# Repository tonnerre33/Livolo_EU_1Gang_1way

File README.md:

# Linovo_EU_1Gang_1way

# What is this ?

It's a livolo EU 1 Gang 1 Way adapter for make it compatible with Mysensors.

You have just to build this node and replace the front plate of your Livolo EU Switch and you'll be able to command your light with your Mysensors controller.

This node is compatible with livolo **EU VL-C701X-2 VER:C0**

# Warning !!

**I'm not responsible if the Livolo manufacturer change the board hardware revision or if you bought the wrong product !**

# Why i'm working with this switch ?

## Run without neutral wire (2 wires system) :

I leave in France and we are only 2 wires for the light switch. 

For the moment, there is no mysensors project for 2 wires installation.

The Linovo EU switch is a 2 wires project !!

## No need more place in your wall :

Who has never been a lack of a place in his wall box ?

This product can be installed in your existing wall box in place of your interruptor without a problem !!

## Touch Pad and beautifull design :

Maybe it's the future ? 

So you'll have an ultimate beauty and you'll be able to command your light with a sensitive touch control feeling like iPhone touch.

## Seems pretty  safe :

I don't know for you, but i am pretty scared about fire with electronic in my walls. 

That's why i don't want to put any electronical card in my walls without case and this switch has a one.

## More informations about the switch :

https://fr.aliexpress.com/item/Free-Shipping-Livolo-Luxury-White-Crystal-Glass-Switch-Panel-EU-Standard-VL-C701-11-110-250V/512886492.html# Livolo_EU_1Gang_1way

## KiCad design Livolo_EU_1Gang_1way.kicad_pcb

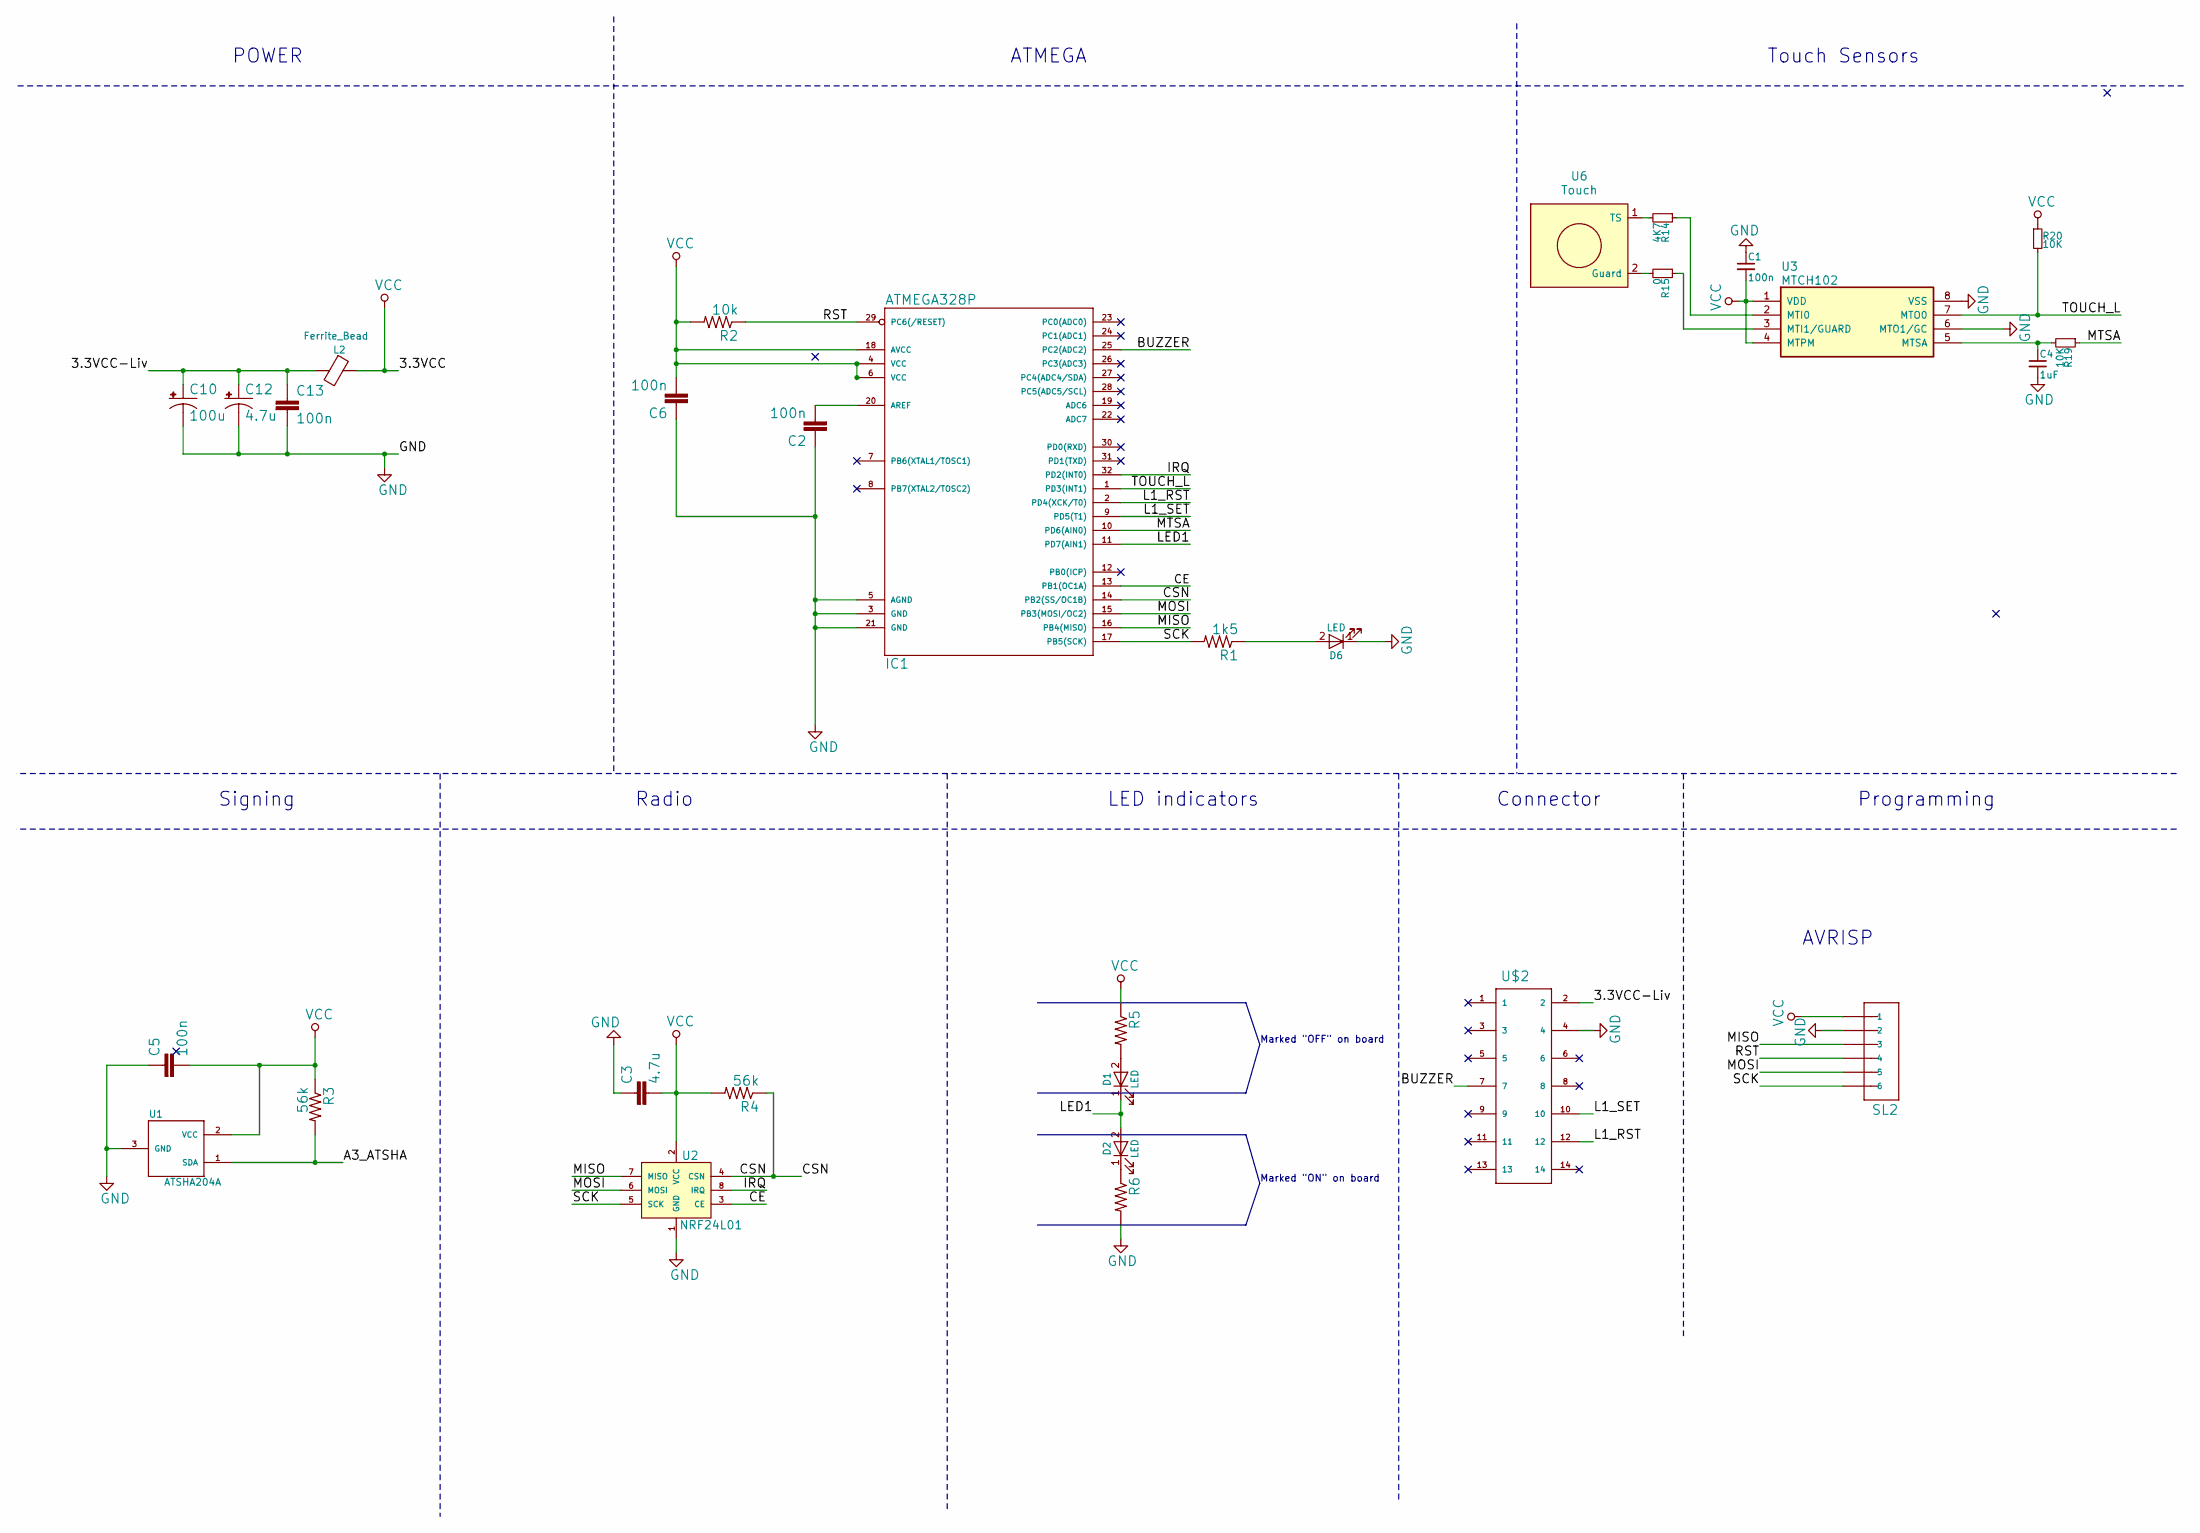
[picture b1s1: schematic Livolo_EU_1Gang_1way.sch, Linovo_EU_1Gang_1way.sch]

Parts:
C1, C5: 100n; C_0603_HandSoldering
C2, C6: 100n; C_0402
C3: 4.7u; C_0603_HandSoldering
C4: 1uF; C_0603_HandSoldering
C10: 100u; EIA3216; Rating X5R/10V
C12: 4.7u; EIA3216; Rating X5R/10V
C13: 100n; C_0603_HandSoldering; Rating X5R/10V
D1, D2, D6: LED; LED_0603
IC1: ATMEGA328P; TQFP32-08
L2: Ferrite_Bead; R_0603_HandSoldering
R1: 1k5; R_0603_HandSoldering
R2: 10k; R_0603_HandSoldering
R3, R4: 56k; R_0603_HandSoldering
R5, R6: R_0603_HandSoldering
R14: 4K7; R_0603
R15: 0; R_0603
R19, R20: 10K; R_0603
SL2: 1X06-1MM
U1: ATSHA204A; SOT23-3
U2: NRF24L01; NRF24L01-SMD
U3: MTCH102; MSOP-8_3x3mm_Pitch0.65mm
U6: Touch; livolo_ts_guard
U$2: CONNECTOR_02_X_072MM_SPACING; CONNECTOR_02_X_07_2MM

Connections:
/3.3VCC-Liv: C10.+, C12.+, C13.1, L2.2, U$2.2
/A3_ATSHA: R3.2, U1.1 (SDA)
/BUZZER: IC1.25 (PC2(ADC2)), U$2.7
/CE: IC1.13 (PB1(OC1A)), U2.3 (CE)
/CSN: IC1.14 (PB2(SS/OC1B)), R4.1, U2.4 (CSN)
/IRQ: IC1.32 (PD2(INT0)), U2.8 (IRQ)
/L1_RST: IC1.2 (PD4(XCK/T0)), U$2.12
/L1_SET: IC1.9 (PD5(T1)), U$2.10
/LED1: D1.1 (K), D2.2 (A), IC1.11 (PD7(AIN1))
/MISO: IC1.16 (PB4(MISO)), SL2.3, U2.7 (MISO)
/MOSI: IC1.15 (PB3(MOSI/OC2)), SL2.5, U2.6 (MOSI)
/MTSA: IC1.10 (PD6(AIN0)), R19.1
/RST: IC1.29 (PC6(/RESET)), R2.1, SL2.4
/SCK: IC1.17 (PB5(SCK)), R1.2, SL2.6, U2.5 (SCK)
/TOUCH_L: IC1.1 (PD3(INT1)), R20.2, U3.7 (MTO0)
GND: C1.1, C2.1, C3.1, C4.2, C5.1, C6.1, C10.-, C12.-, C13.2, D6.1 (K), IC1.3 (GND), IC1.5 (AGND), IC1.21 (GND), R6.2, SL2.2, U1.3 (GND), U2.1 (GND), U3.6 (MTO1/GC), U3.8 (VSS), U$2.4
unnamed: C2.2, IC1.20 (AREF)
unnamed: C4.1, R19.2, U3.5 (MTSA)
unnamed: D1.2 (A), R5.2
unnamed: D2.1 (K), R6.1
unnamed: D6.2 (A), R1.1
unnamed: R14.1, U3.2 (MTI0)
unnamed: R14.2, U6.1 (TS)
unnamed: R15.1, U3.3 (MTI1/GUARD)
unnamed: R15.2, U6.2 (Guard)
VCC: C1.2, C3.2, C5.2, C6.2, IC1.4 (VCC), IC1.6 (VCC), IC1.18 (AVCC), L2.1, R2.2, R3.1, R4.2, R5.1, R20.1, SL2.1, U1.2 (VCC), U2.2 (VCC), U3.1 (VDD), U3.4 (MTPM)

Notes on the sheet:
Programming
AVRISP
Touch Sensors
ATMEGA
POWER
Signing
Radio
LED indicators
Marked "OFF" on board
Marked "ON" on board
Connector

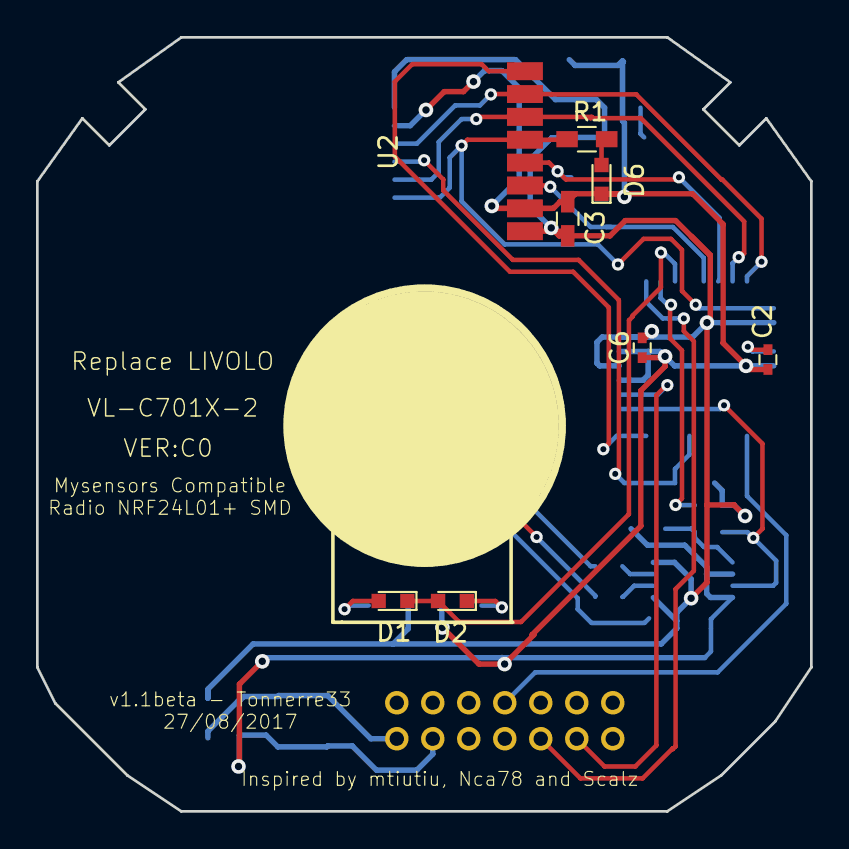
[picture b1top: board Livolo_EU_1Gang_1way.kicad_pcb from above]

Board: 2 copper layers, 43.0 x 43.0 mm, 30 parts (0 on the bottom side), 26 nets.

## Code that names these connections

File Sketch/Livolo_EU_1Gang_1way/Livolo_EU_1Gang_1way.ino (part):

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int ledPins[] = {7};
byte buttonPins[] = {3};
const uint8_t RELAY_CH_PINS[][2] = {
    {5, 4} // channel 1 relay control pins(bistable relay - 2 coils) {L1_SET, L1_RST}

};
#define MTSA_PIN 6
#define BUZZER_PIN A2


const uint32_t RELAY_PULSE_DELAY_MS = 40; //Def 50
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    // initialize led, relays pins as outputs and buttons as inputs

    //SENSIBILITY
    pinMode(MTSA_PIN, OUTPUT);
    analogWrite(MTSA_PIN, 255 - settings.button_sensiblity * 255/100);
    //BUZZER
    pinMode(BUZZER_PIN, OUTPUT);
    digitalWrite(BUZZER_PIN, LOW);
    for (int i = 0; i < NUMBER_OF_BUTTONS; i++) {
        //LEDS
        pinMode(ledPins[i], OUTPUT);
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        if((millis() - lastMode) >= MODE_CLEANING_MS && MODE[i] == MODE_CLEANING) {
            MODE[0] = settings.mode_def[0];
            MODE[1] = settings.mode_def[1];
            blinkNumberOutput(1, BUZZER_PIN,100,100);
             for (int i = 0; i < NUMBER_OF_BUTTONS; i++) {
                digitalWrite(ledPins[i],  getChannelState(i));
             }
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                        switchLight(i+1, channelState[i]);
                        EndWaitFalseTrigger[i] = true;
                    } else {
                        blinkNumberOutput(1, BUZZER_PIN,100,100);
                    }
                }
            }
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                        MODE[i] = MODE_NORMAL;
                        channelState[i] = ON;
                        switchLight(i+1, channelState[i]); // No buzzer on the sleep power
                        blinkNumberOutput(2, BUZZER_PIN,100,100);
                    }
                    if(lastTouchTimestamp[i] >= LONG_TOUCH_DETECT_CLEANING_MS) {
                        MODE[0] = MODE_CLEANING;
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                        lastMode = millis();
                        channelState[i] = ON;
                        switchLight(i+1, channelState[i]); // No buzzer on the sleep power 
                        blinkNumberOutput(1, BUZZER_PIN,100,100);
                    }
                }
            }
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                if(millis() - lastTouchTimestamp[i] >= LONG_TOUCH_DETECT_THRESHOLD_MS && MODE[i] != MODE_NORMAL
                        && channelState[i] == ON) { // No buzzer on the sleep power
                    MODE[i] = MODE_NORMAL;
                    blinkNumberOutput(2, BUZZER_PIN,100,100);
                }
                if(millis() - lastTouchTimestamp[i] >= LONG_TOUCH_DETECT_CLEANING_MS && MODE[i] != MODE_CLEANING
                        && channelState[i] == ON) { // No buzzer on the sleep power
                    MODE[0] = MODE_CLEANING;
                    MODE[1] = MODE_CLEANING;
                    lastMode = millis();
                    blinkNumberOutput(1, BUZZER_PIN,100,100);
                }

            }
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
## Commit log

2017-08-08 v1.0.beta
2017-08-08 adding Gerber & pdf
2017-08-27 move MTSA pin to a PWM pin of the ATMEGA
2017-08-27 remove resistor for guard
2017-10-04 Added sketch
2017-11-05 optimise code for settings by the air
2017-11-05 added MY_TRANSPORT_WAIT_READY_MS
